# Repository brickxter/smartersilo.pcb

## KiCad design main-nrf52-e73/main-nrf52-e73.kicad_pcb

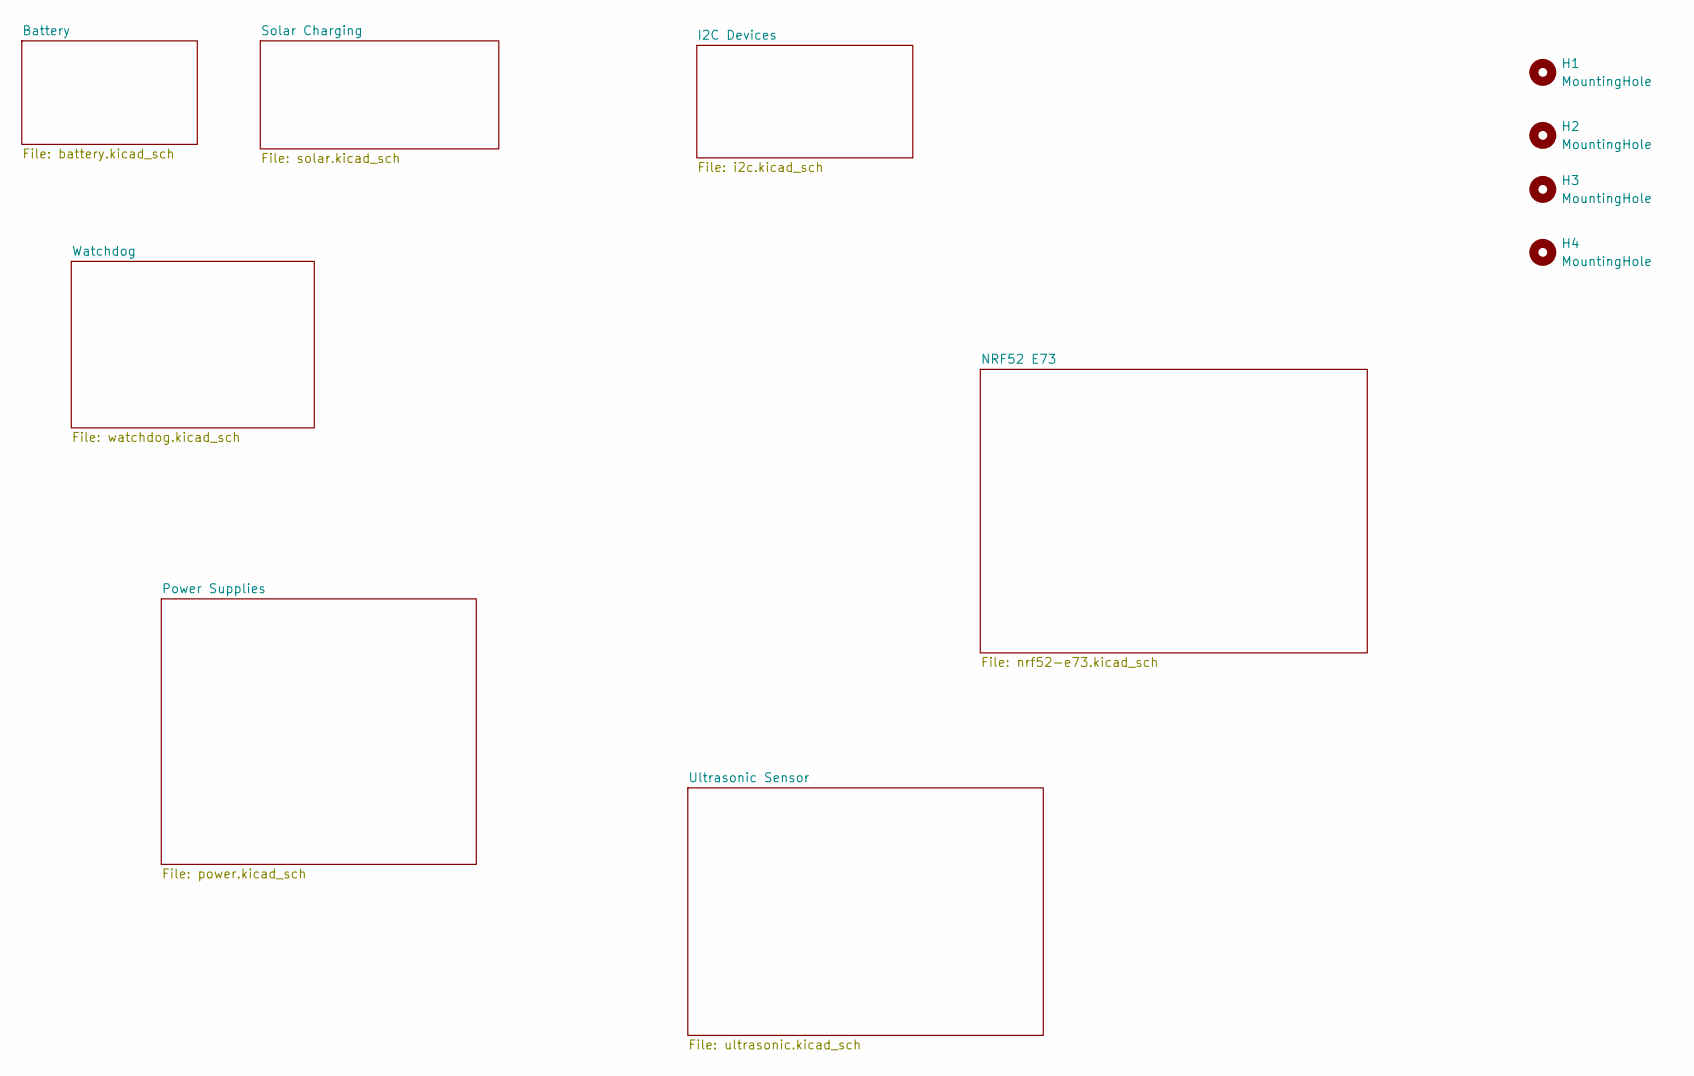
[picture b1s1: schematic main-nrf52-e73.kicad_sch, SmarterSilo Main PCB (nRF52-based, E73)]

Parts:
H1, H2, H3, H4: MountingHole; MountingHole_3.5mm

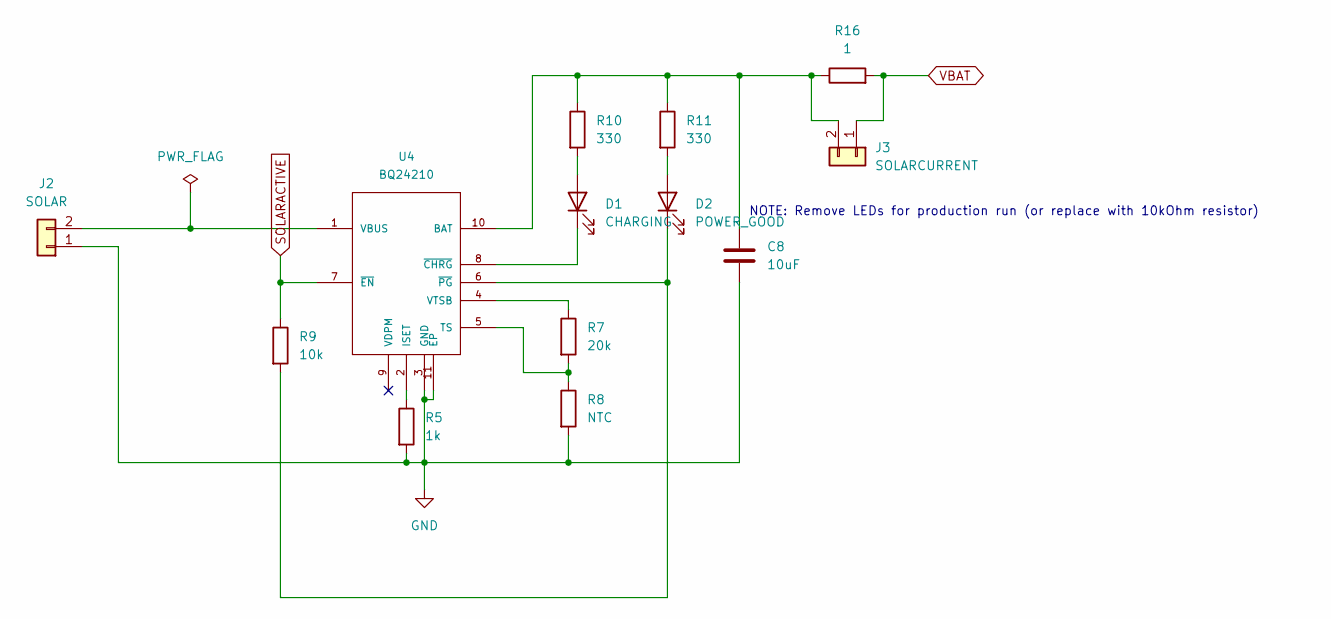
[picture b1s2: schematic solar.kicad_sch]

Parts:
C8: 10uF; C_0805_2012Metric; LCSC C15850
D1: CHARGING; LED_0603_1608Metric; LCSC C2286
D2: POWER_GOOD; LED_0603_1608Metric; LCSC C2286
J2: SOLAR; PinHeader_1x02_P2.54mm_Vertical
J3: SOLARCURRENT; PinHeader_1x02_P2.54mm_Vertical
R5: 1k; R_0603_1608Metric; LCSC C21190
R7: 20k; R_0603_1608Metric; LCSC C4184
R8: NTC; R_0603_1608Metric; LCSC C76589
R9: 10k; R_0603_1608Metric; LCSC C25804
R10, R11: 330; R_0603_1608Metric; LCSC C23138
R16: 1; R_0603_1608Metric; LCSC C22936
U4: BQ24210; WSON-10-1EP_2.5x2.5mm_P0.5mm_EP1.2x2mm; LCSC C524795

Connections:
GND: C8.2, J2.1, R5.2, R8.2, U4.3 (GND), U4.11 (EP); also elsewhere on the board
unnamed: D1.2 (A), R10.2
unnamed: D1.1 (K), U4.8 (~CHRG)
unnamed: D2.2 (A), R11.2
unnamed: D2.1 (K), R9.2, U4.6 (~PG)
unnamed: J2.2, U4.1 (VBUS)
unnamed: C8.1, J3.2, R10.1, R11.1, R16.1, U4.10 (BAT)
unnamed: R5.1, U4.2 (ISET)
unnamed: R7.2, R8.1, U4.5 (TS)
unnamed: R7.1, U4.4 (VTSB)
SOLARACTIVE: R9.1, U4.7 (~EN); also elsewhere on the board
VBAT: J3.1, R16.2; also elsewhere on the board

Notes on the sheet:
NOTE: Remove LEDs for production run (or replace with 10kOhm resistor)

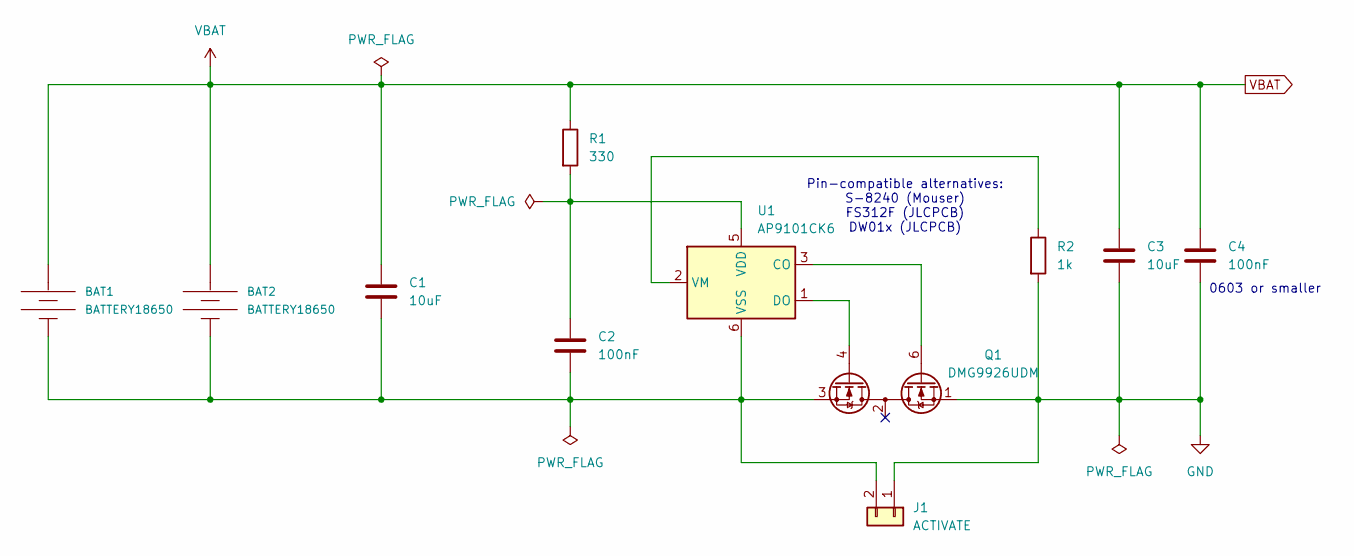
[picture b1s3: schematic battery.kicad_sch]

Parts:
BAT1, BAT2: BATTERY18650; MyParts-BATTERY_18650-HOLDER
C1, C3: 10uF; C_0805_2012Metric; LCSC C15850
C2, C4: 100nF; C_0603_1608Metric; LCSC C14663
J1: ACTIVATE; PinHeader_1x02_P2.54mm_Vertical
Q1: DMG9926UDM; SOT-23-6; LCSC C156289
R1: 330; R_0603_1608Metric; LCSC C23138
R2: 1k; R_0603_1608Metric; LCSC C21190
U1: AP9101CK6; SOT-23-6; LCSC C151339

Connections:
GND: C3.2, C4.2, J1.1, Q1.1 (D1), R2.2; also elsewhere on the board
unnamed: BAT1.GND@ (-), BAT2.GND@ (-), C1.2, C2.2, J1.2, Q1.3 (S2), U1.6 (VSS)
unnamed: Q1.6 (G1), U1.3 (CO)
unnamed: Q1.4 (G2), U1.1 (DO)
unnamed: C2.1, R1.2, U1.5 (VDD)
unnamed: R2.1, U1.2 (VM)
VBAT: BAT1.PWR@ (+), BAT2.PWR@ (+), C1.1, C3.1, C4.1, R1.1; also elsewhere on the board

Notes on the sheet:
0603 or smaller
Pin-compatible alternatives: S-8240 (Mouser) FS312F (JLCPCB) DW01x (JLCPCB)

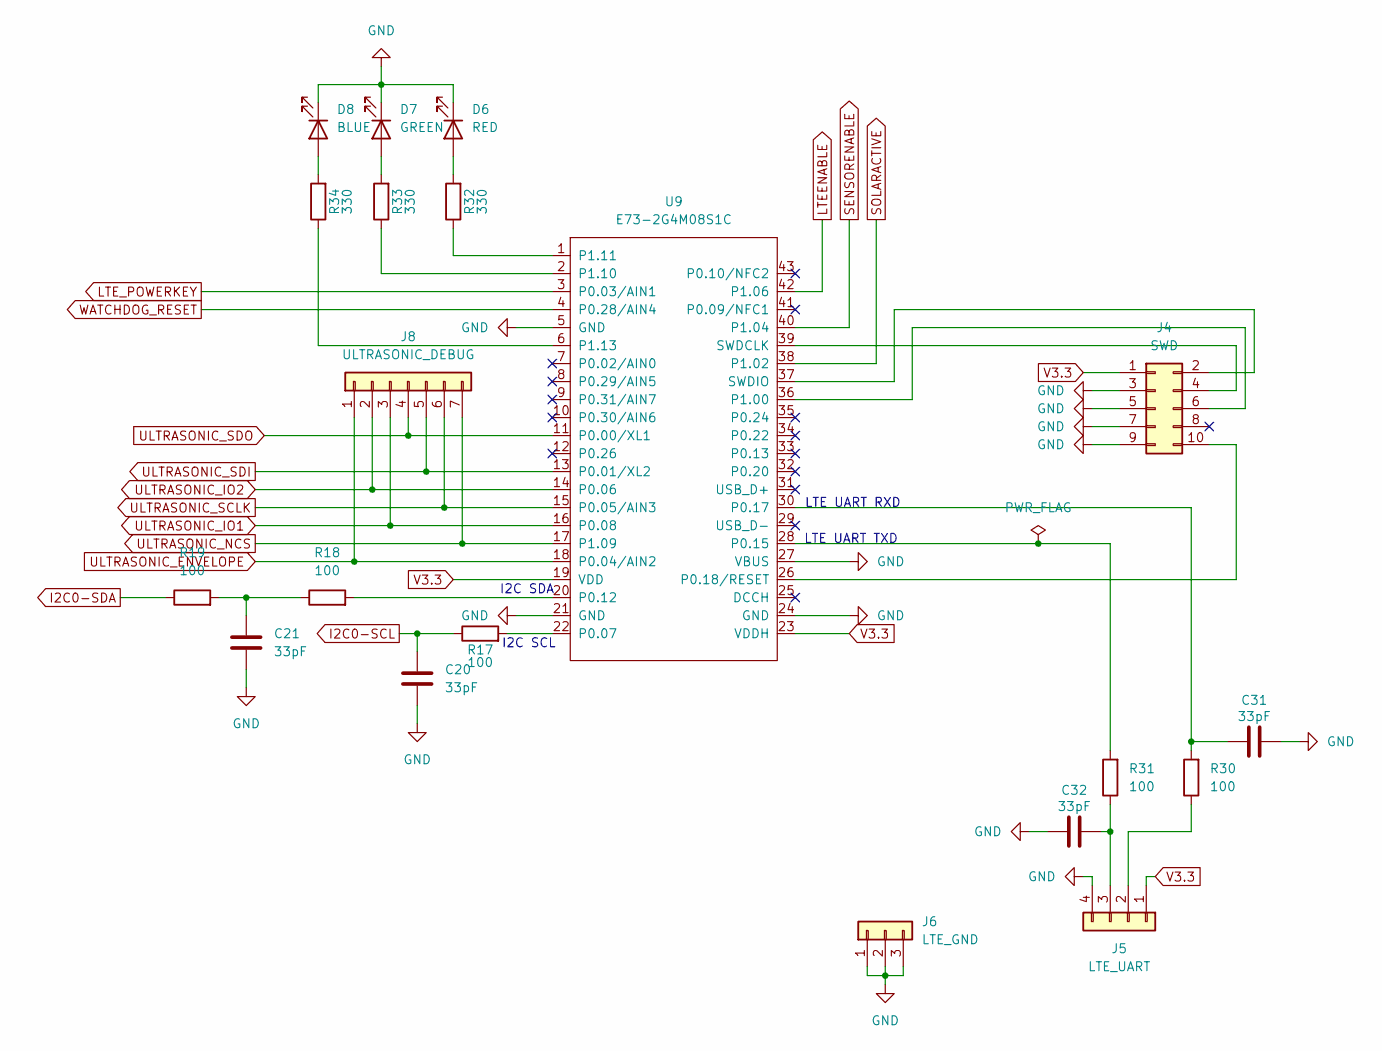
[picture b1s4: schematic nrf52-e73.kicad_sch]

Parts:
C20, C21, C31, C32: 33pF; C_0603_1608Metric; LCSC C1663
D6: RED; LED_0603_1608Metric; LCSC C2286
D7: GREEN; LED_0603_1608Metric; LCSC C12624
D8: BLUE; LED_0603_1608Metric; LCSC C2288
J4: SWD; PinHeader_2x05_P1.27mm_Vertical_SMD
J5: LTE_UART; PinHeader_1x04_P2.54mm_Vertical
J6: LTE_GND; PinHeader_1x03_P2.54mm_Vertical
J8: ULTRASONIC_DEBUG; PinHeader_1x07_P2.54mm_Vertical
R17, R18, R19, R30, R31: 100; R_0603_1608Metric; LCSC C22775
R32, R33, R34: 330; R_0603_1608Metric; LCSC C23138
U9: E73-2G4M08S1C; E73(2G4M08S1C); LCSC C356849

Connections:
GND: C20.2, C21.2, C31.2, C32.1, D6.1 (K), D7.1 (K), D8.1 (K), J4.3, J4.5, J4.7, J4.9, J5.4, J6.1, J6.2, J6.3, U9.5 (GND), U9.21 (GND), U9.24 (GND), U9.27 (VBUS); also elsewhere on the board
I2C0-SCL: C20.1, R17.1; also elsewhere on the board
I2C0-SDA: R19.1; also elsewhere on the board
LTEENABLE: U9.42 (P1.06); also elsewhere on the board
LTE_POWERKEY: U9.3 (P0.03/AIN1); also elsewhere on the board
unnamed: C21.1, R18.1, R19.2
unnamed: D6.2 (A), R32.2
unnamed: D7.2 (A), R33.2
unnamed: D8.2 (A), R34.2
unnamed: J4.2, U9.37 (SWDIO)
unnamed: J4.4, U9.39 (SWDCLK)
unnamed: J4.6, U9.36 (P1.00)
unnamed: J4.10, U9.26 (P0.18/RESET)
unnamed: J5.2, R30.1
unnamed: C32.2, J5.3, R31.1
unnamed: R17.2, U9.22 (P0.07)
unnamed: R18.2, U9.20 (P0.12)
unnamed: R31.2, U9.28 (P0.15)
unnamed: C31.1, R30.2, U9.30 (P0.17)
unnamed: R33.1, U9.2 (P1.10)
unnamed: R32.1, U9.1 (P1.11)
unnamed: R34.1, U9.6 (P1.13)
SENSORENABLE: U9.40 (P1.04); also elsewhere on the board
SOLARACTIVE: U9.38 (P1.02); also elsewhere on the board
ULTRASONIC_ENVELOPE: J8.1, U9.18 (P0.04/AIN2); also elsewhere on the board
ULTRASONIC_IO1: J8.3, U9.16 (P0.08); also elsewhere on the board
ULTRASONIC_IO2: J8.2, U9.14 (P0.06); also elsewhere on the board
ULTRASONIC_NCS: J8.7, U9.17 (P1.09); also elsewhere on the board
ULTRASONIC_SCLK: J8.6, U9.15 (P0.05/AIN3); also elsewhere on the board
ULTRASONIC_SDI: J8.5, U9.13 (P0.01/XL2); also elsewhere on the board
ULTRASONIC_SDO: J8.4, U9.11 (P0.00/XL1); also elsewhere on the board
V3.3: J4.1, J5.1, U9.19 (VDD), U9.23 (VDDH); also elsewhere on the board
WATCHDOG_RESET: U9.4 (P0.28/AIN4); also elsewhere on the board

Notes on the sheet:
I2C SDA
I2C SCL
LTE UART TXD
LTE UART RXD

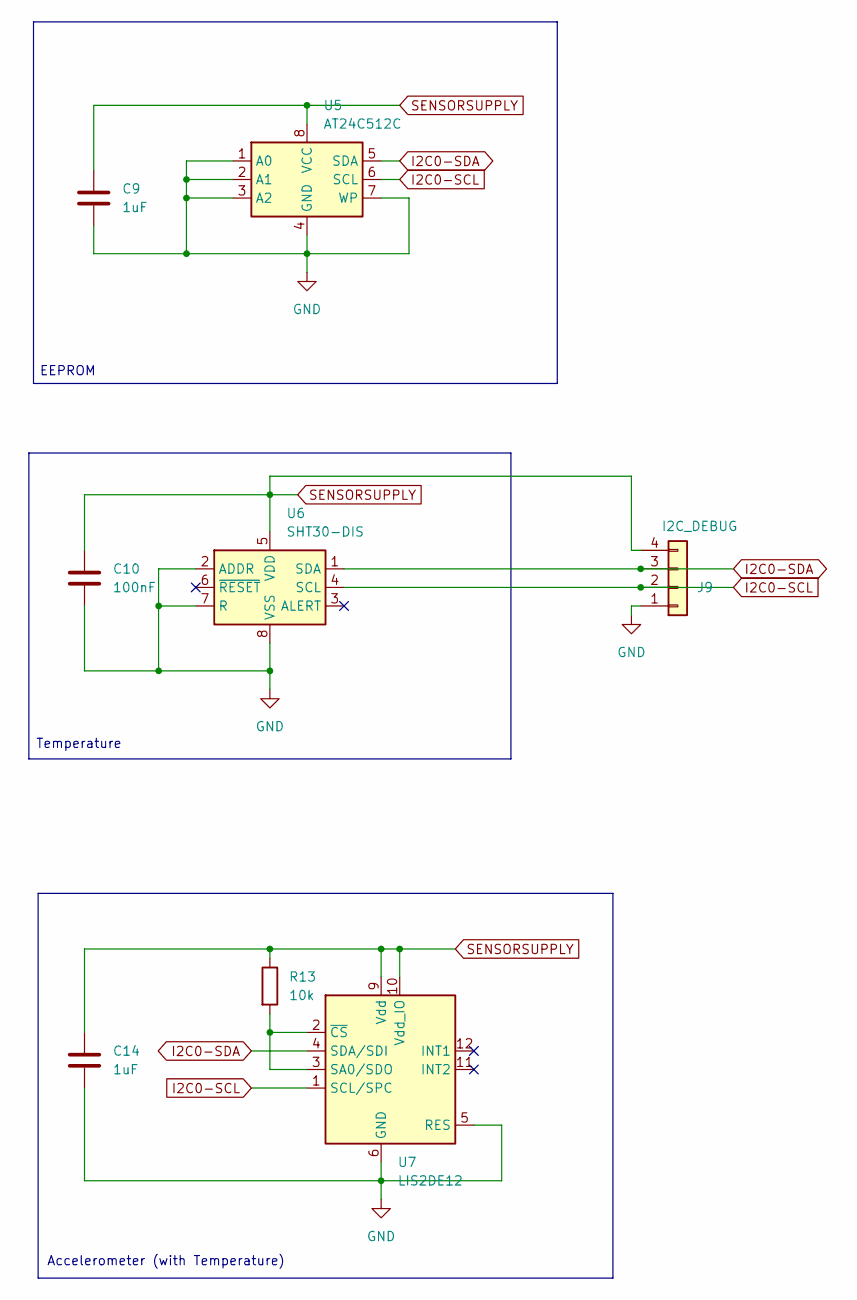
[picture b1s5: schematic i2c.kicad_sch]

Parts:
C9, C14: 1uF; C_0805_2012Metric; LCSC C28323
C10: 100nF; C_0603_1608Metric; LCSC C14663
J9: I2C_DEBUG; PinHeader_1x04_P2.54mm_Vertical
R13: 10k; R_0603_1608Metric; LCSC C25804
U5: AT24C512C; SOIC-8_3.9x4.9mm_P1.27mm; LCSC C12371
U6: SHT30-DIS; Sensirion_DFN-8-1EP_2.5x2.5mm_P0.5mm_EP1.1x1.7mm; LCSC C77361
U7: LIS2DE12; LGA-12_2x2mm_P0.5mm; LCSC C110926

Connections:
GND: C9.2, C10.2, C14.2, J9.1, U5.1 (A0), U5.2 (A1), U5.3 (A2), U5.4 (GND), U5.7 (WP), U6.2 (ADDR), U6.7 (R), U6.8 (VSS), U6.9 (VSS), U7.5 (RES), U7.6 (GND), U7.7 (GND), U7.8 (GND); also elsewhere on the board
I2C0-SCL: J9.2, U5.6 (SCL), U6.4 (SCL), U7.1 (SCL/SPC); also elsewhere on the board
I2C0-SDA: J9.3, U5.5 (SDA), U6.1 (SDA), U7.4 (SDA/SDI); also elsewhere on the board
unnamed: R13.2, U7.2 (~CS), U7.3 (SA0/SDO)
SENSORSUPPLY: C9.1, C10.1, C14.1, J9.4, R13.1, U5.8 (VCC), U6.5 (VDD), U7.9 (Vdd), U7.10 (Vdd_IO); also elsewhere on the board

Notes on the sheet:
EEPROM
Temperature
Accelerometer (with Temperature)

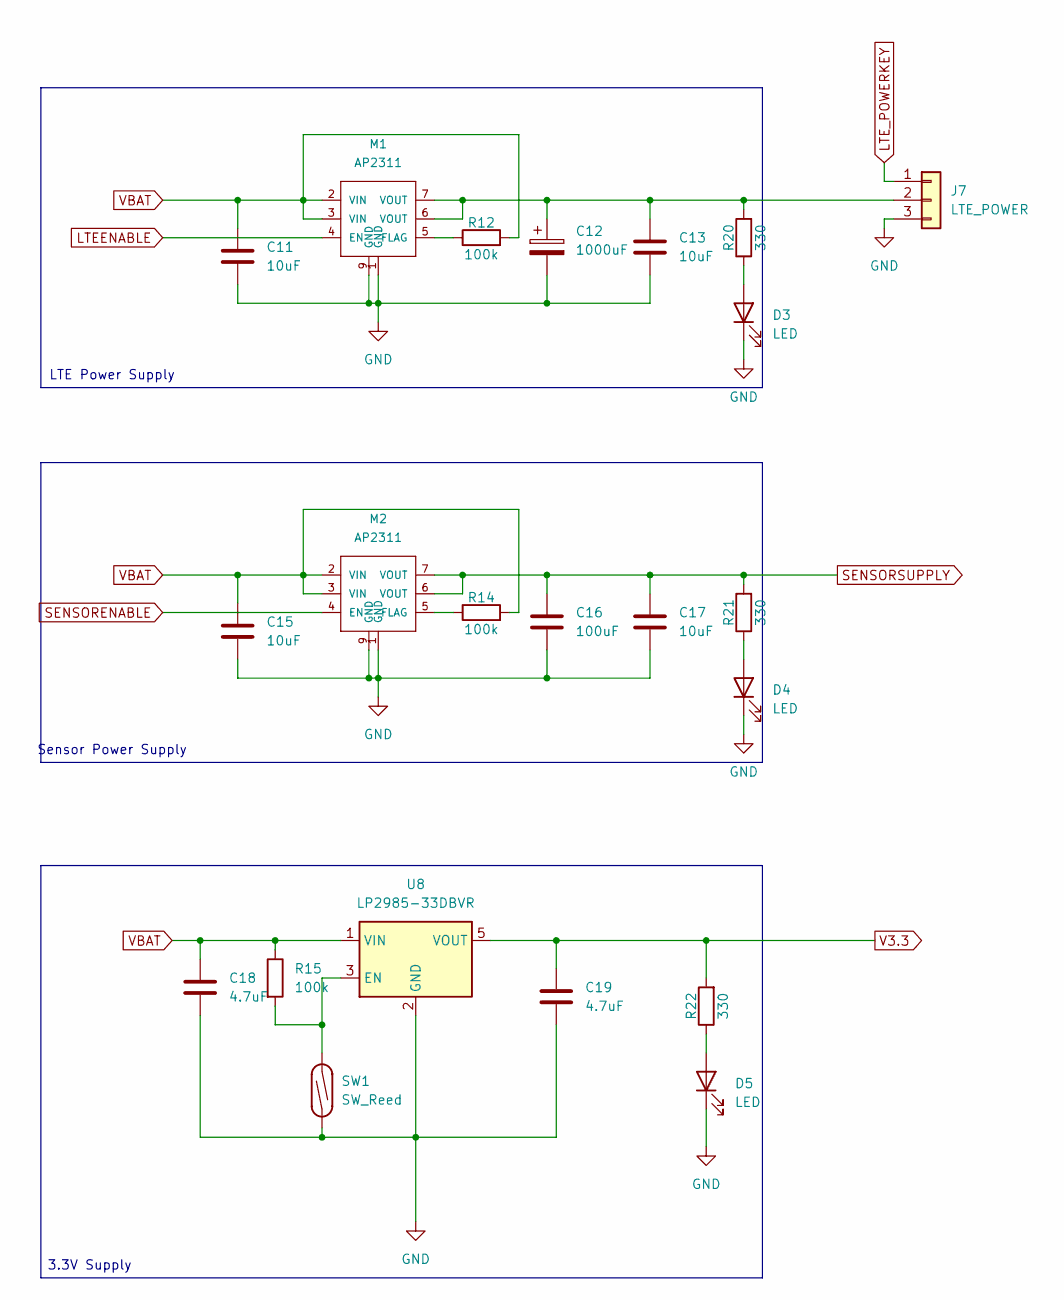
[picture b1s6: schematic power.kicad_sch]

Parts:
C11, C13, C15, C17: 10uF; C_0805_2012Metric; LCSC C15850
C12: 1000uF; CP_Elec_10x10.5; LCSC C263979
C16: 100uF; C_1206_3216Metric; LCSC C15008
C18, C19: 4.7uF; C_0805_2012Metric; LCSC C1779
D3, D4, D5: LED; LED_0603_1608Metric; LCSC C2286
J7: LTE_POWER; PinHeader_1x03_P2.54mm_Vertical
M1, M2: AP2311; MSOP-8-1EP_3x3mm_P0.65mm_EP1.68x1.88mm; LCSC C460351
R12, R14, R15: 100k; R_0603_1608Metric; LCSC C25803
R20, R21, R22: 330; R_0603_1608Metric; LCSC C23138
SW1: SW_Reed; SW_SPST_REED_CT10-XXXX-G1
U8: LP2985-33DBVR; SOT-23-5; LCSC C95414

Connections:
GND: C11.2, C12.2, C13.2, C15.2, C16.2, C17.2, C18.2, C19.2, D3.1 (K), D4.1 (K), D5.1 (K), J7.3, M1.1 (GND), M1.9 (GND), M2.1 (GND), M2.9 (GND), SW1.1, U8.2 (GND); also elsewhere on the board
LTEENABLE: M1.4 (EN); also elsewhere on the board
LTE_POWERKEY: J7.1; also elsewhere on the board
unnamed: D3.2 (A), R20.1
unnamed: D4.2 (A), R21.1
unnamed: D5.2 (A), R22.1
unnamed: C12.1, C13.1, J7.2, M1.6 (VOUT), M1.7 (VOUT), R20.2
unnamed: M1.5 (FLAG), R12.1
unnamed: M2.5 (FLAG), R14.1
unnamed: R15.2, SW1.2, U8.3 (EN)
SENSORENABLE: M2.4 (EN); also elsewhere on the board
SENSORSUPPLY: C16.1, C17.1, M2.6 (VOUT), M2.7 (VOUT), R21.2; also elsewhere on the board
V3.3: C19.1, R22.2, U8.5 (VOUT); also elsewhere on the board
VBAT: C11.1, C15.1, C18.1, M1.2 (VIN), M1.3 (VIN), M2.2 (VIN), M2.3 (VIN), R12.2, R14.2, R15.1, U8.1 (VIN); also elsewhere on the board

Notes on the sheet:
Sensor Power Supply
3.3V Supply
LTE Power Supply

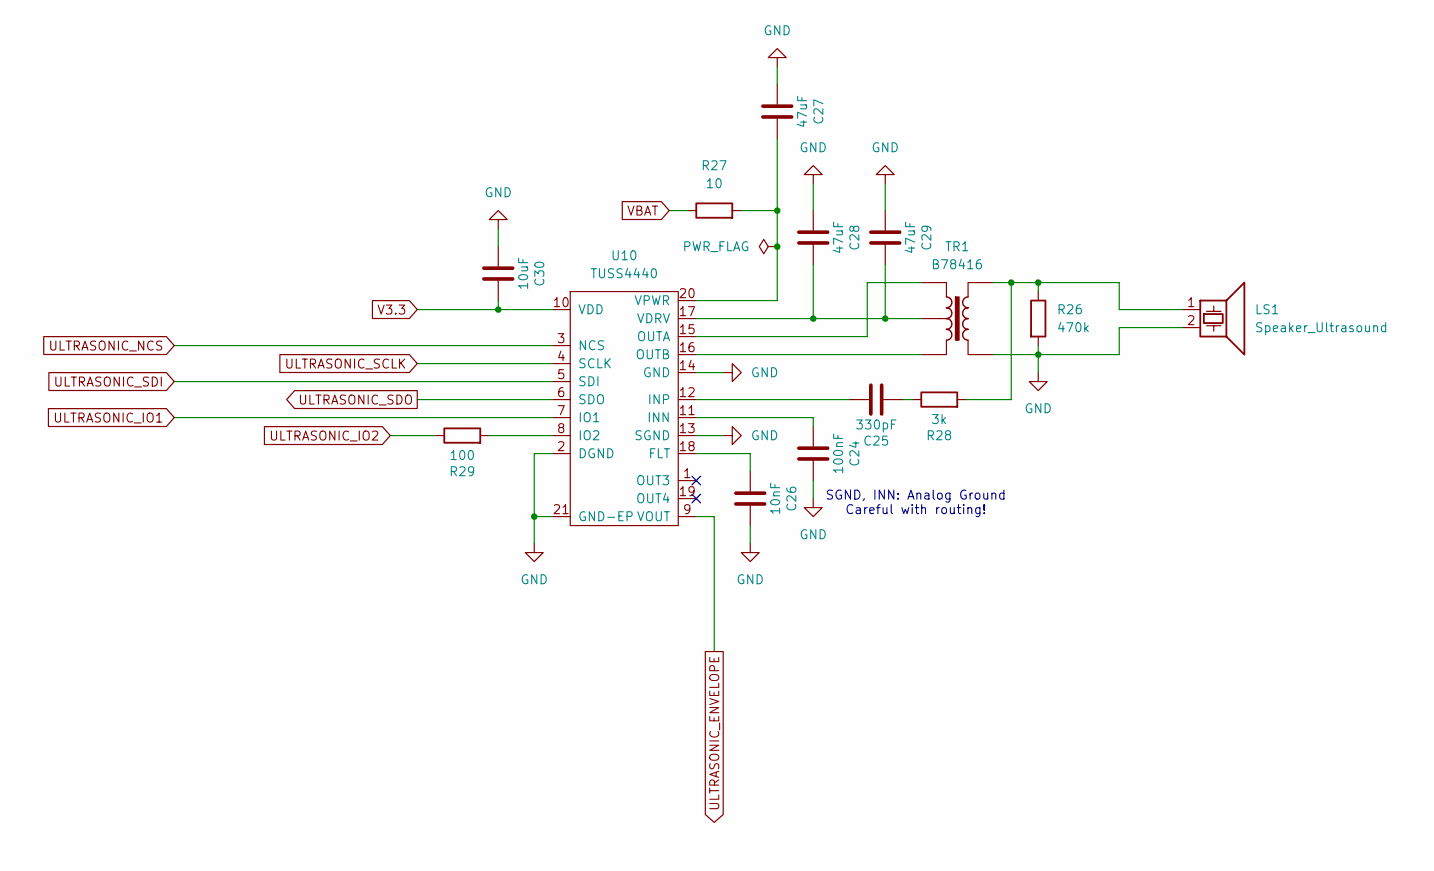
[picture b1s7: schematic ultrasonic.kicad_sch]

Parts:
C24: 100nF; C_0603_1608Metric; LCSC C14663
C25: 330pF; C_0603_1608Metric; LCSC C1664
C26: 10nF; C_0603_1608Metric; LCSC C57112
C27, C28, C29: 47uF; C_1206_3216Metric; LCSC C96123
C30: 10uF; C_0805_2012Metric; LCSC C15850
LS1: Speaker_Ultrasound; 400EP250-Holes
R26: 470k; R_0603_1608Metric; LCSC C23178
R27: 10; R_0603_1608Metric; LCSC C22859
R28: 3k; R_0603_1608Metric; LCSC C4211
R29: 100; R_0603_1608Metric; LCSC C22775
TR1: B78416
U10: TUSS4440; QFN-20-1EP_4x4mm_P0.5mm_EP2.6x2.6mm; LCSC C1855778

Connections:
GND: C24.2, C26.2, C27.1, C28.1, C29.1, C30.1, LS1.2, R26.2, TR1.4, U10.2 (DGND), U10.13 (SGND), U10.14 (GND), U10.21 (GND-EP); also elsewhere on the board
unnamed: C25.1, R28.1
unnamed: LS1.1, R26.1, R28.2, TR1.5
unnamed: C26.1, U10.18 (FLT)
unnamed: C24.1, U10.11 (INN)
unnamed: C25.2, U10.12 (INP)
unnamed: R29.2, U10.8 (IO2)
unnamed: TR1.1, U10.15 (OUTA)
unnamed: TR1.3, U10.16 (OUTB)
unnamed: C28.2, C29.2, TR1.2, U10.17 (VDRV)
unnamed: C27.2, R27.2, U10.20 (VPWR)
ULTRASONIC_ENVELOPE: U10.9 (VOUT); also elsewhere on the board
ULTRASONIC_IO1: U10.7 (IO1); also elsewhere on the board
ULTRASONIC_IO2: R29.1; also elsewhere on the board
ULTRASONIC_NCS: U10.3 (NCS); also elsewhere on the board
ULTRASONIC_SCLK: U10.4 (SCLK); also elsewhere on the board
ULTRASONIC_SDI: U10.5 (SDI); also elsewhere on the board
ULTRASONIC_SDO: U10.6 (SDO); also elsewhere on the board
V3.3: C30.2, U10.10 (VDD); also elsewhere on the board
VBAT: R27.1; also elsewhere on the board

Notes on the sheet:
SGND, INN: Analog Ground Careful with routing!

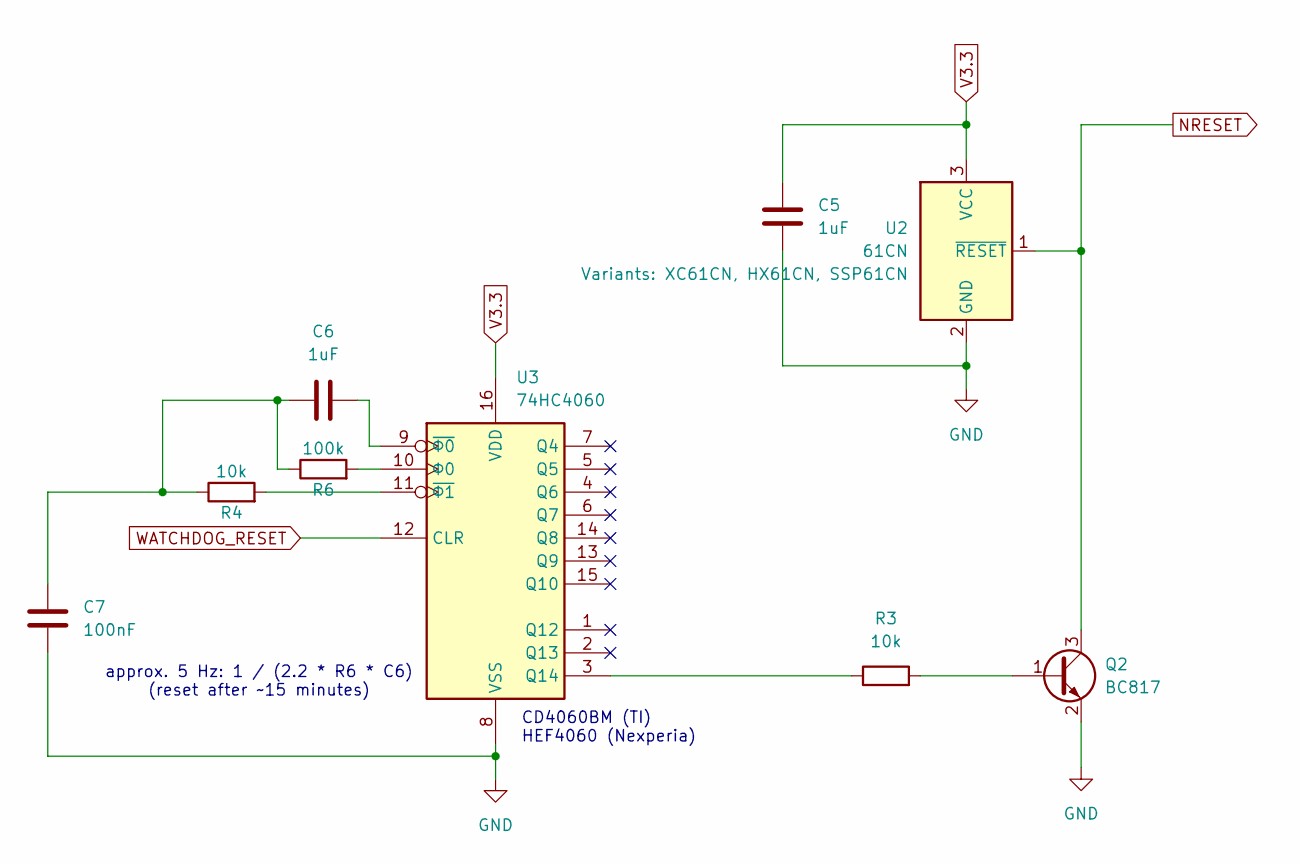
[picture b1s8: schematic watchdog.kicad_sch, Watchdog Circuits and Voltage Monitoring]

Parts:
C5, C6: 1uF; C_0805_2012Metric; LCSC C28323
C7: 100nF; C_0603_1608Metric; LCSC C14663
Q2: BC817; SOT-23; LCSC C444722
R3, R4: 10k; R_0603_1608Metric; LCSC C25804
R6: 100k; R_0603_1608Metric; LCSC C25803
U2: 61CN; SOT-23; LCSC C112138
U3: 74HC4060; TSSOP-16_4.4x5mm_P0.65mm; LCSC C32699

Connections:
GND: C5.2, C7.1, Q2.2 (E), U2.2 (GND), U3.8 (VSS); also elsewhere on the board
NRESET: Q2.3 (C), U2.1 (~RESET)
unnamed: C6.1, C7.2, R4.1, R6.1
unnamed: Q2.1 (B), R3.2
unnamed: R3.1, U3.3 (Q14)
unnamed: C6.2, U3.9 (~Φ0)
unnamed: R4.2, U3.11 (~Φ1)
unnamed: R6.2, U3.10 (Φ0)
V3.3: C5.1, U2.3 (VCC), U3.16 (VDD); also elsewhere on the board
WATCHDOG_RESET: U3.12 (CLR); also elsewhere on the board

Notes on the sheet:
CD4060BM (TI) HEF4060 (Nexperia)
approx. 5 Hz: 1 / (2.2 * R6 * C6) (reset after ~15 minutes)

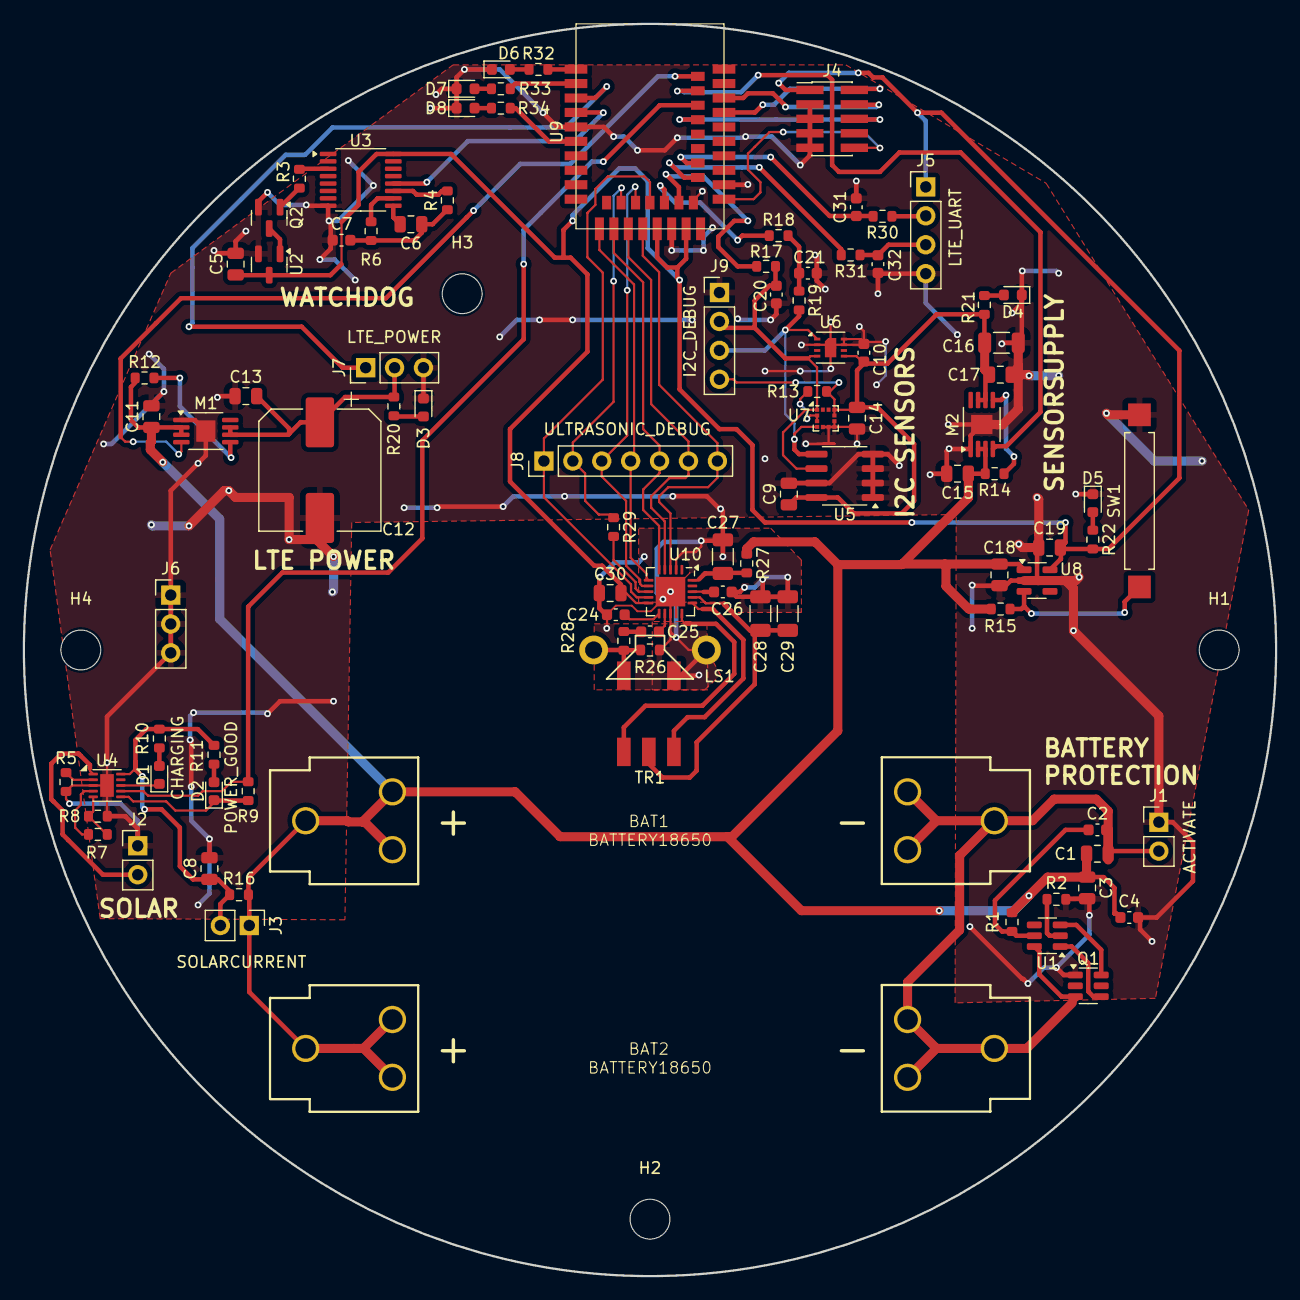
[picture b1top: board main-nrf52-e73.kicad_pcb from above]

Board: 2 copper layers, 110.0 x 110.0 mm, 101 parts (0 on the bottom side), 74 nets.

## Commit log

2024-12-02 main-nrf52-e73: Populated with first schematic.
    PCB routing still pending.
2024-12-10 Finished first prototype of nRF52 powered main PCB.
    Using Ebyte E73 module for the nRF chip.
